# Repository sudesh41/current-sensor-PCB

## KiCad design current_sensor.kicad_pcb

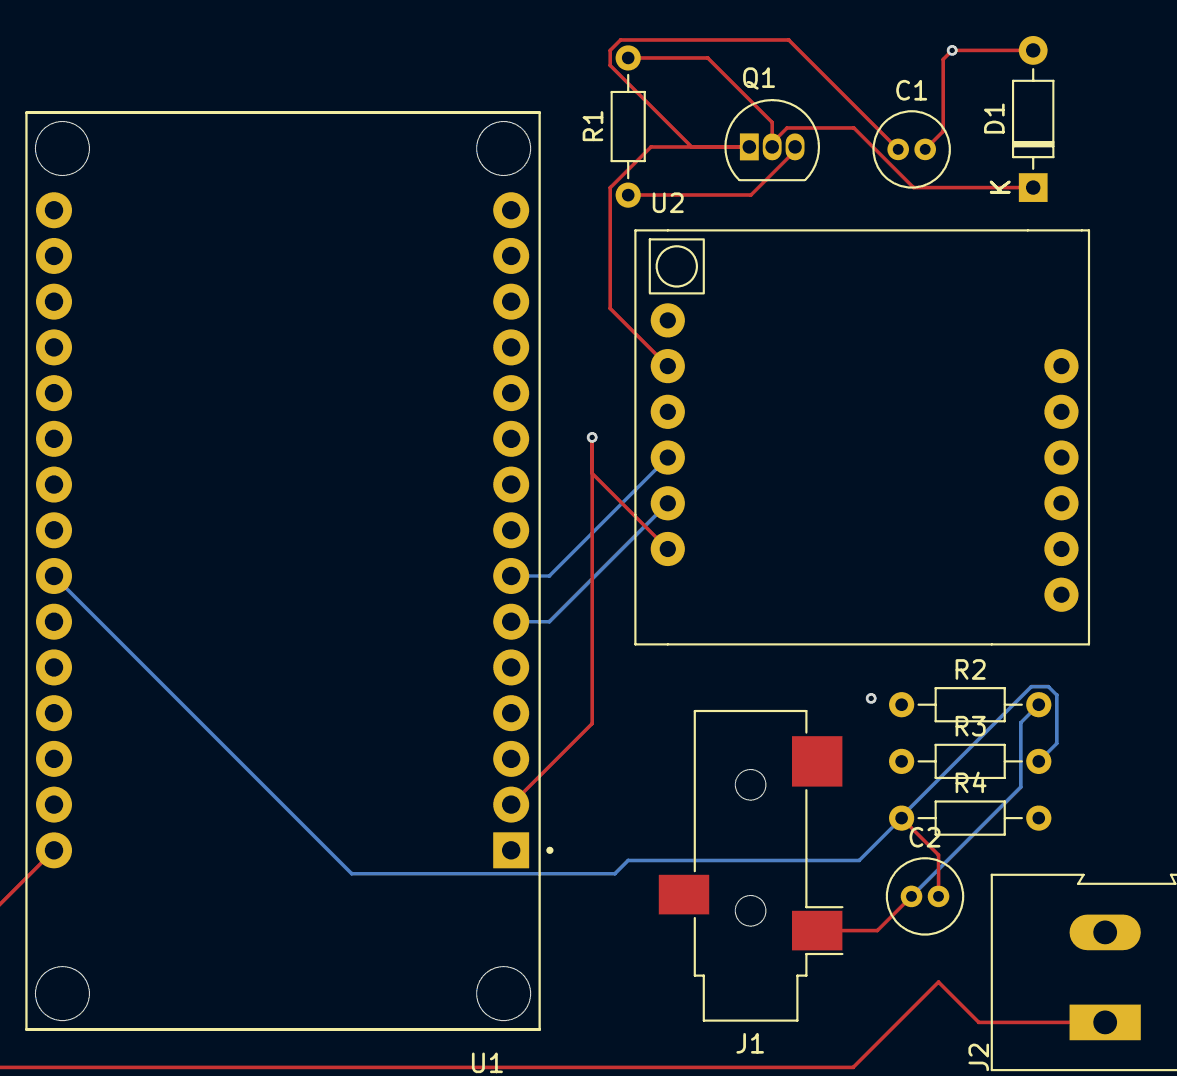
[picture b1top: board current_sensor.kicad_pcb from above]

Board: 2 copper layers, 12 parts (0 on the bottom side), 8 nets.

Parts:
C1, C2: C; C_Radial_D4.0mm_H7.0mm_P1.50mm
D1: D_Zener; D_DO-35_SOD27_P7.62mm_Horizontal
J1: AudioPlug2; Jack_3.5mm_CUI_SJ-3523-SMT_Horizontal
J2: Screw_Terminal_01x02; TerminalBlock_Altech_AK300-2_P5.00mm
Q1: 2N3904; TO-92_Inline
R1, R2, R3, R4: R; R_Axial_DIN0204_L3.6mm_D1.6mm_P7.62mm_Horizontal
U1: ESP32-DEVKIT-V1; MODULE_ESP32_DEVKIT_V1
U2: SIM800L-CORE

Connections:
GND: C1.2, D1.2 (A), J1.T, J2.2, R2.1, R3.1, U1.2 (GND), U1.29 (GND), U2.6 (GND)
unnamed: C2.1, J1.S, R2.2
unnamed: D1.1 (K), Q1.2 (B), R1.2
unnamed: J2.1, Q1.3 (C), R1.1, R4.2, U1.30 (VIN)
unnamed: C1.1, Q1.1 (E), U2.2 (VCC)
unnamed: C2.2, R3.2, R4.1, U1.24 (D26)
unnamed: U1.6 (RX2), U2.5 (TXD)
unnamed: U1.7 (TX2), U2.4 (RXD)
